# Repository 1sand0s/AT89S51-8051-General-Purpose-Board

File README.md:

# AT89S51 8051 General Purpose Board

<h2> What is it? </h2>
This is a breakout for AT89S51 that I used during my research at UT Austin. The objective was to study the vulnerability of firmware running on the AT89S51 to Electromagnetic (EM) Side-Channel attacks. 

<h2> What we accomplished </h2>

1. We were successful in writing an instruction dissassembler that was able to dissassemble firmware with up to 98% accuracy using the EM side-channel
 
2. We were successful in writing a cycle level EM trace simulator that is capable of synthesizing EM trace corresponding to a firmware running on the AT89S51 with up to 90% accuracy

3. We used the cycle level EM trace simulator to successfully predict control flow leakge of the firmware and optimize it to show a decrease in control flow leakage  
<h2> What the repository contains ? </h2>

The AT89s51 directory contains the board design files. The PCB layouting was done in Kicad. The Bootloader directory contains a powershell script to simplify the usage of avr_dude.exe while burning the HEX file onto the board and the config file describes fuse settings, chip erase details and so on specific to the 8051 to avr_dude.

Please refer to https://1sand0s.github.io/make-your-own-8051at89s51-board.html for more details

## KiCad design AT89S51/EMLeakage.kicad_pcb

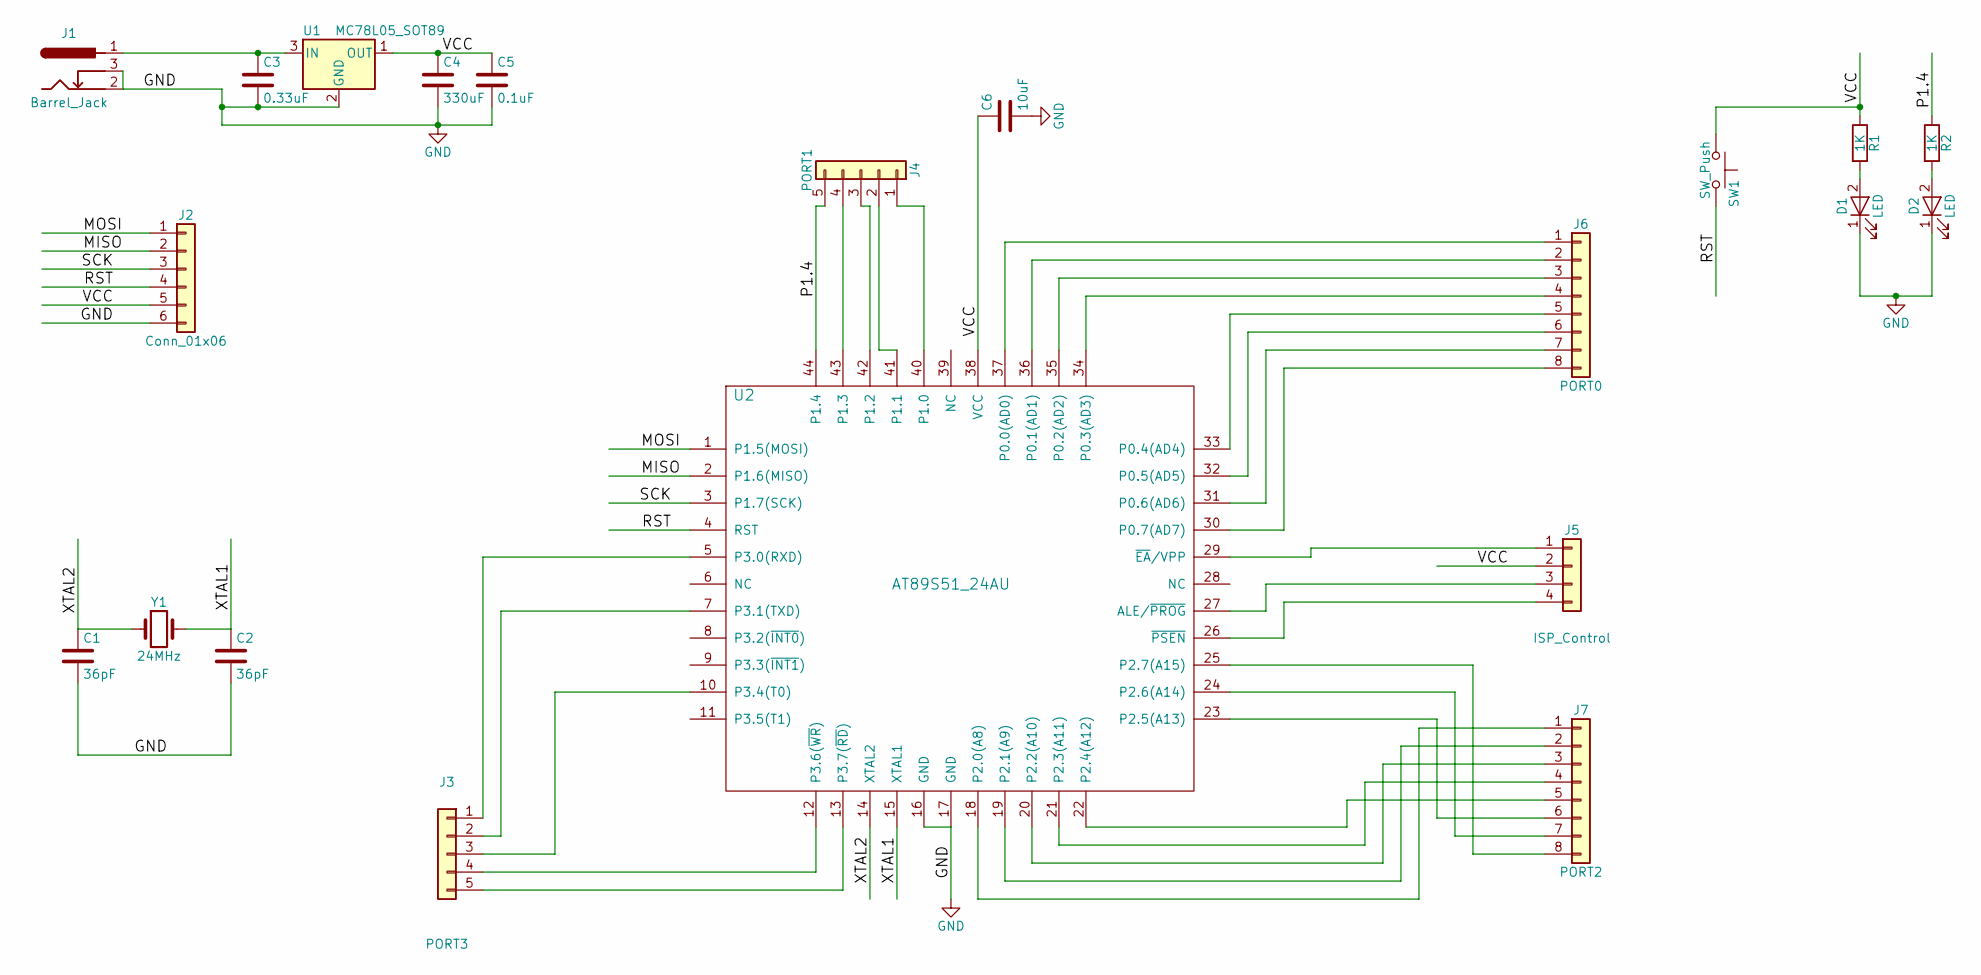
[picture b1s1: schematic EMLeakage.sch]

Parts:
C1, C2: 36pF; C_0805_HandSoldering
C3: 0.33uF; C_0805_HandSoldering
C4: 330uF; CP_Radial_D10.0mm_P2.50mm
C5: 0.1uF; C_0805_HandSoldering
C6: 10uF; C_0805_HandSoldering
D1, D2: LED; LED_0805_HandSoldering
J1: Barrel_Jack; BARREL_JACK
J2: Conn_01x06; Pin_Header_Straight_1x06_Pitch1.00mm
J3: PORT3; Pin_Header_Straight_1x05_Pitch1.00mm
J4: PORT1; Pin_Header_Straight_1x05_Pitch1.00mm
J5: ISP_Control; Pin_Header_Straight_1x04_Pitch1.00mm
J6: PORT0; Pin_Header_Straight_1x08_Pitch1.00mm
J7: PORT2; Pin_Header_Straight_1x08_Pitch1.00mm
R1, R2: 1K; R_0805
SW1: SW_Push; SW_SPST_SKQG
U1: MC78L05_SOT89; SOT89-3_Housing
U2: AT89S51_24AU; TQFP-44_10x10mm_Pitch0.8mm
Y1: 24MHz; Crystal_AT310_d3.0mm_l10.0mm_Vertical

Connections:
/MISO: J2.2, U2.2 (P1.6(MISO))
/MOSI: J2.1, U2.1 (P1.5(MOSI))
/P1.4: J4.5, R2.1, U2.44 (P1.4)
/RST: J2.4, SW1.2, U2.4 (RST)
/SCK: J2.3, U2.3 (P1.7(SCK))
/VCC: C4.1, C5.1, C6.1, J2.5, J5.2, R1.1, SW1.1, U1.1 (OUT), U2.38 (VCC)
/XTAL1: C2.1, U2.15 (XTAL1), Y1.2
/XTAL2: C1.1, U2.14 (XTAL2), Y1.1
GND: C1.2, C2.2, C3.2, C4.2, C5.2, C6.2, D1.1 (K), D2.1 (K), J1.2, J1.3, J2.6, U1.2 (GND), U2.16 (GND), U2.17 (GND)
unnamed: C3.1, J1.1, U1.3 (IN)
unnamed: D1.2 (A), R1.2
unnamed: D2.2 (A), R2.2
unnamed: J3.1, U2.5 (P3.0(RXD))
unnamed: J3.2, U2.7 (P3.1(TXD))
unnamed: J3.3, U2.10 (P3.4(T0))
unnamed: J3.4, U2.12 (P3.6(~WR))
unnamed: J3.5, U2.13 (P3.7(~RD))
unnamed: J4.1, U2.40 (P1.0)
unnamed: J4.2, U2.41 (P1.1)
unnamed: J4.3, U2.42 (P1.2)
unnamed: J4.4, U2.43 (P1.3)
unnamed: J5.1, U2.29 (~EA~/VPP)
unnamed: J5.3, U2.27 (ALE/~PROG)
unnamed: J5.4, U2.26 (~PSEN)
unnamed: J6.1, U2.37 (P0.0(AD0))
unnamed: J6.2, U2.36 (P0.1(AD1))
unnamed: J6.3, U2.35 (P0.2(AD2))
unnamed: J6.4, U2.34 (P0.3(AD3))
unnamed: J6.5, U2.33 (P0.4(AD4))
unnamed: J6.6, U2.32 (P0.5(AD5))
unnamed: J6.7, U2.31 (P0.6(AD6))
unnamed: J6.8, U2.30 (P0.7(AD7))
unnamed: J7.1, U2.18 (P2.0(A8))
unnamed: J7.2, U2.19 (P2.1(A9))
unnamed: J7.3, U2.20 (P2.2(A10))
unnamed: J7.4, U2.21 (P2.3(A11))
unnamed: J7.5, U2.22 (P2.4(A12))
unnamed: J7.6, U2.23 (P2.5(A13))
unnamed: J7.7, U2.24 (P2.6(A14))
unnamed: J7.8, U2.25 (P2.7(A15))

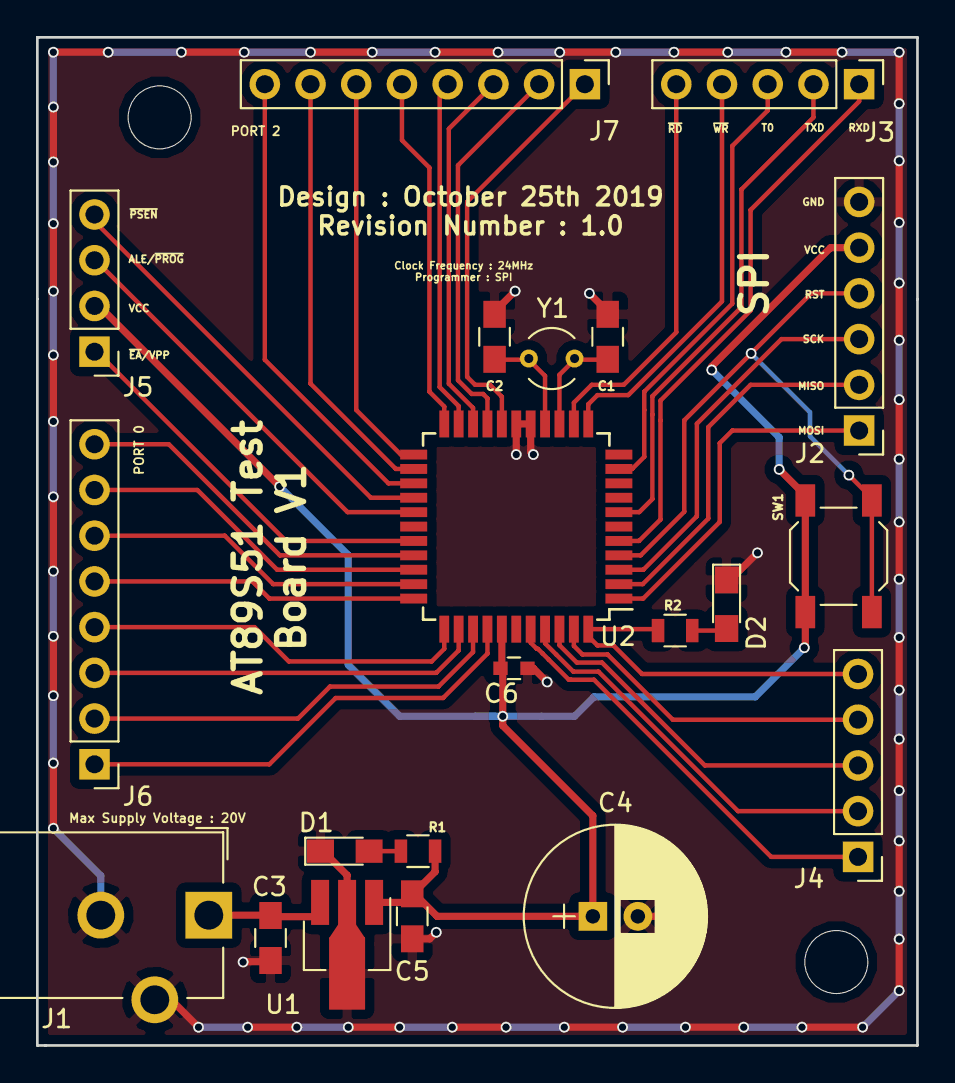
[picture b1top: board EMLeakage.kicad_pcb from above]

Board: 2 copper layers, 48.9 x 56.0 mm, 21 parts (0 on the bottom side), 40 nets.

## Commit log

2019-12-05 Adding 8051 Board Kicad Project
2019-12-05 Uploading the Bootloader script for abstracting avr_dude and simplifying uploading code to the 8051 board
2021-12-13 Create LICENSE
2021-12-13 Adding versioning and licensing details
2022-03-11 Updating Readme
